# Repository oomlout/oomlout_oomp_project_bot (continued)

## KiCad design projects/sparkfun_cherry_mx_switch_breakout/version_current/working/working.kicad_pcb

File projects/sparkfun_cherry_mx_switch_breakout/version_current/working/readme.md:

# OOMP Project  
## Cherry_MX_Switch_Breakout  by sparkfun  
  
oomp key: oomp_projects_flat_sparkfun_cherry_mx_switch_breakout  
(snippet of original readme)  
  
SparkFun Cherry MX Switch Breakout  
====================  
  
<table class="table table-hover table-striped table-bordered">  
  <tr align="center">  
   <td></td>  
   <td></td>  
  </tr>  
  <tr align="center">  
    <td><i>SparkFun Cherry MX Switch Breakout </i></td>  
    <td><i>Cherry MX Switch Soldered on Breakout</i></td>  
  </tr>  
</table>  
  
[*SparkFun Cherry MX Switch Breakout (BOB-13773)*](https://www.sparkfun.com/products/13773)  
  
Cherry MX Keyswitches are top-of-the-line mechanical keyboard switches. They’re satisfyingly “clicky”, reliable up to tens-of-millions of key presses, and a standard in gaming and programming keyboards across the globe. With the SparkFun Cherry MX Switch Breakout we have made the switches more easily adaptable to breadboard or perfboard-based projects. The Cherry MX Switch Breakout is a perfect prototyping tool for projects ranging from a single-key user-input to fully-custom 101-key keyboards.  
  
Repository Contents  
-------------------  
  
* **/Hardware** - All Eagle design files (.brd, .sch)  
* **/Production** - Production panel files (.brd)  
  
Documentation  
--------------  
* **[Hookup Guide](https://learn.sparkfun.com/tutorials/cherr  
  full source readme at [readme_src.md](readme_src.md)  
  
source repo at: [https://github.com/sparkfun/Cherry_MX_Switch_Breakout](https://github.com/sparkfun/Cherry_MX_Switch_Breakout)  
## Board  

## Schematic  

[schematic pdf](working_schematic.pdf)  
## Images

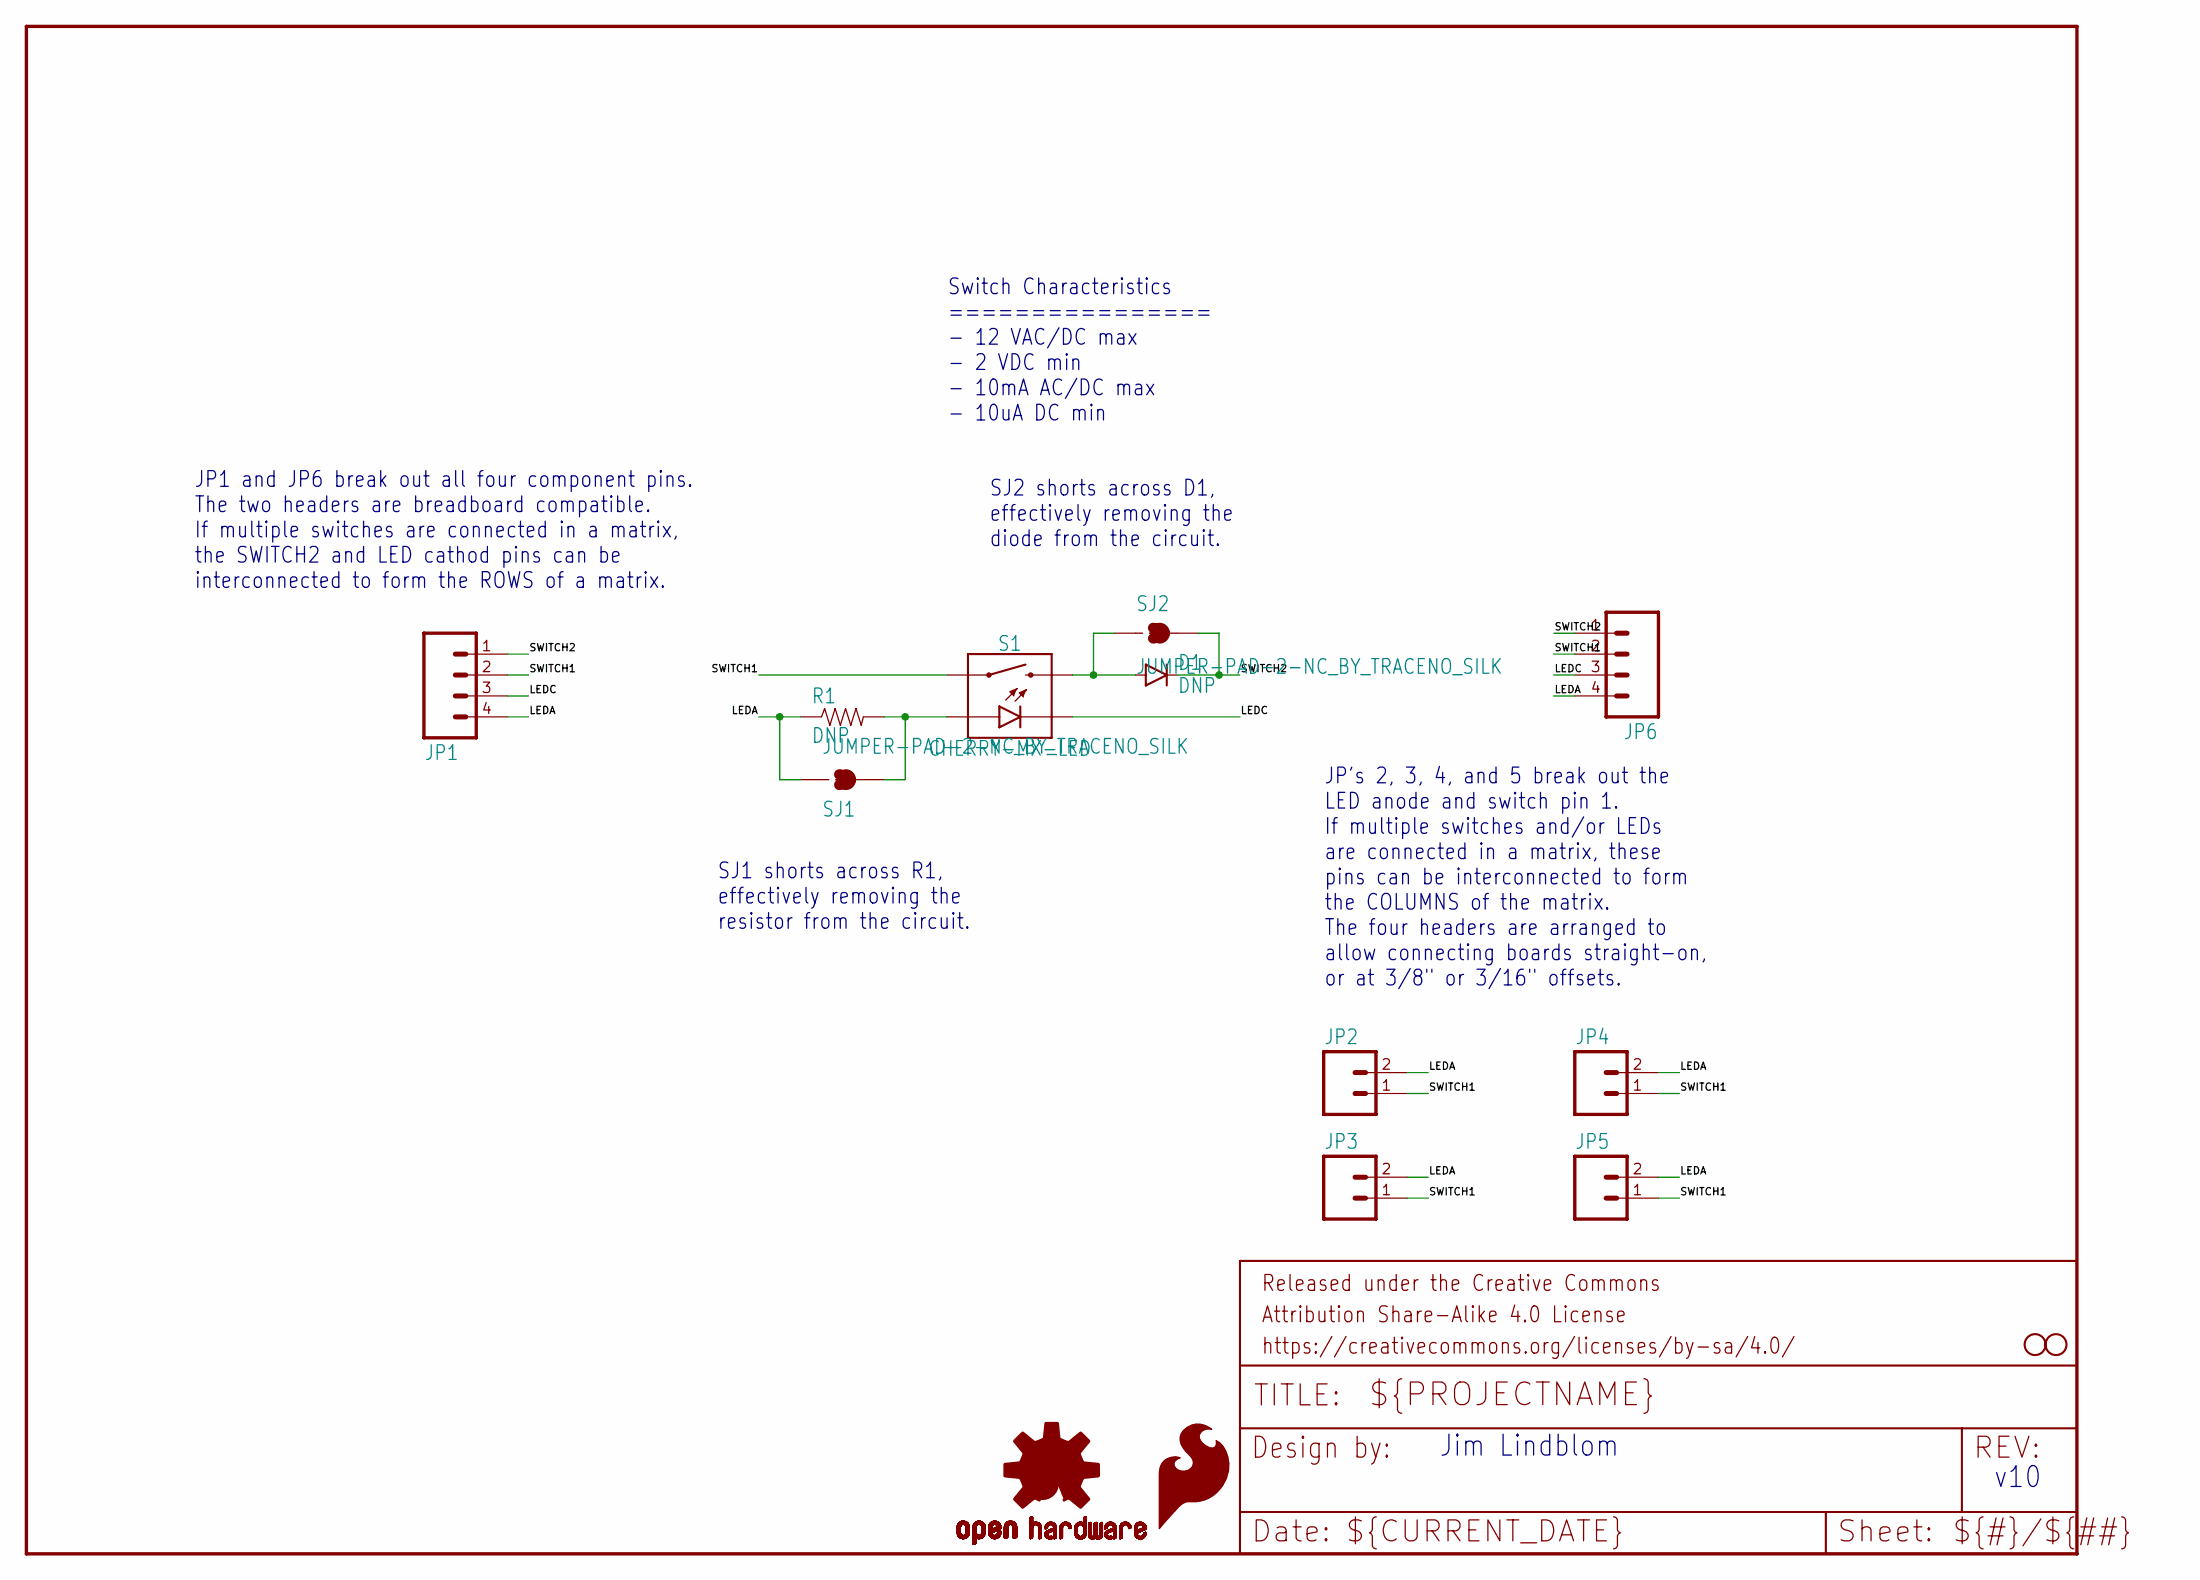
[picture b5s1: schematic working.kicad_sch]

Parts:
D1: DNP; DIODE-PTH-0.1
FRAME1: FRAME-LETTER; CREATIVE_COMMONS
JP1, JP6: M04NO_SILK_ALL_ROUND; 1X04_NO_SILK_ALL_ROUND
JP2, JP3, JP4, JP5: M021X02_NO_SILK; 1X02_NO_SILK
LOGO1: OSHW-LOGOS; OSHW-LOGO-S
LOGO2: SFE_LOGO_FLAME.1_INCH; SFE_LOGO_FLAME_.1
R1: DNP; AXIAL-0.1
S1: CHERRY-MX-LED
SJ1, SJ2: JUMPER-PAD-2-NC_BY_TRACENO_SILK; PAD-JUMPER-2-NC_BY_TRACE_NO_SILK
STANDOFF1, STANDOFF2: STAND-OFF2-56; STAND-OFF-2-56

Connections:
LEDA: JP1.4, JP2.2, JP3.2, JP4.2, JP5.2, JP6.4, R1.P$1 (1), SJ1.1
LEDC: JP1.3, JP6.3, S1.K (C)
unnamed: R1.P$2 (2), S1.A, SJ1.2
unnamed: D1.A, S1.S2, SJ2.1
SWITCH1: JP1.2, JP2.1, JP3.1, JP4.1, JP5.1, JP6.2, S1.S1
SWITCH2: D1.C, JP1.1, JP6.1, SJ2.2

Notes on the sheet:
SJ2 shorts across D1, effectively removing the diode from the circuit.
JP1 and JP6 break out all four component pins. The two headers are breadboard compatible. If multiple switches are connected in a matrix, the SWITCH2 and LED cathod pins can be interconnected to form the ROWS of a matrix.
v10
JP's 2, 3, 4, and 5 break out the LED anode and switch pin 1. If multiple switches and/or LEDs are connected in a matrix, these pins can be interconnected to form the COLUMNS of the matrix. The four headers are arranged to allow connecting boards straight-on, or at 3/8" or 3/16" offsets.
Jim Lindblom
SJ1 shorts across R1, effectively removing the resistor from the circuit.
Switch Characteristics ================ - 12 VAC/DC max - 2 VDC min - 10mA AC/DC max - 10uA DC min

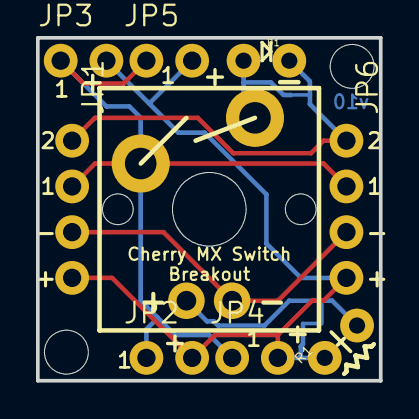
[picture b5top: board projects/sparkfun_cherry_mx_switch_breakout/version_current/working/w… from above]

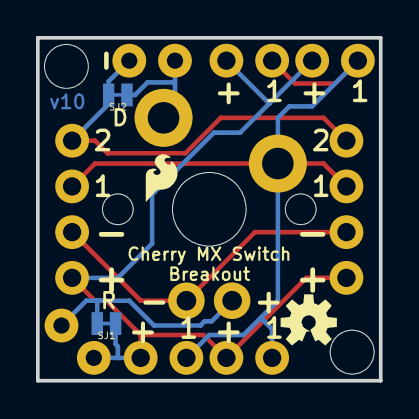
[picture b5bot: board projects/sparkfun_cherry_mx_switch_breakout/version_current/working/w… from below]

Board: 2 copper layers, 19.1 x 19.0 mm, 16 parts (4 on the bottom side), 6 nets.

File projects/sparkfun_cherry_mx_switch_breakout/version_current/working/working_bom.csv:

Row,Description,Part,References,Value,Footprint,Quantity Per PCB,Status,Datasheet
1,,FRAME-LETTER,FRAME1,FRAME-LETTER,CREATIVE_COMMONS,1, ,
2,,M021X02_NO_SILK,JP2 JP3 JP4 JP5,M021X02_NO_SILK,1X02_NO_SILK,4, ,
3,,M04NO_SILK_ALL_ROUND,JP1 JP6,M04NO_SILK_ALL_ROUND,1X04_NO_SILK_ALL_ROUND,2, ,
4,,OSHW-LOGOS,LOGO1,OSHW-LOGOS,OSHW-LOGO-S,1, ,
5,,SFE_LOGO_FLAME.1_INCH,LOGO2,SFE_LOGO_FLAME.1_INCH,SFE_LOGO_FLAME_.1,1, ,
6,,CHERRY-MX-LED,S1,CHERRY-MX-LED,CHERRY-MX-LED,1, ,
7,,JUMPER-PAD-2-NC_BY_TRACENO_SILK,SJ1 SJ2,JUMPER-PAD-2-NC_BY_TRACENO_SILK,PAD-JUMPER-2-NC_BY_TRACE_NO_SILK,2, ,
8,,STAND-OFF2-56,STANDOFF1 STANDOFF2,STAND-OFF2-56,STAND-OFF-2-56,2, ,





Project info:
Schematic:,working
Variant:,default
Revision:,
Date:,2023-08-06_12-56-00
KiCad Version:,7.0.6-7.0.6~ubuntu22.04.1
Statistics:
Component Groups:,10
Component Count:,16 (0 SMD/ 0 THT)
Fitted Components:,14 (0 SMD/ 0 THT)
Number of PCBs:,1
Total Components:,14

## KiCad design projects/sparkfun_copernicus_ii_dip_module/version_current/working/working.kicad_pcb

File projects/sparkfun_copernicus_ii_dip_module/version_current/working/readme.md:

# OOMP Project  
## Copernicus_II_DIP_Module  by sparkfun  
  
oomp key: oomp_projects_flat_sparkfun_copernicus_ii_dip_module  
(snippet of original readme)  
  
Copernicus II DIP Module  
========================  

[*Copernicus II DIP Module (GPS-11858)*](https://www.sparkfun.com/products/11858)  
  
This breakout board allows access to the SMD pins of the Copernicus II GPS module from Trimble.   
  
Repository Contents  
-------------------  
* **/Hardware** - All Eagle design files (.brd, .sch)  
* **/Libraries** - All Arduino libraries and board examples  
* **/Production** - Test bed files and production panel files  
  
Documentation  
-------------------  
* **[Hookup Guide](https://learn.sparkfun.com/tutorials/copernicus-ii-hookup-guide)** - Basic hookup guide  
  
Version History  
---------------  
* [GPS-11067 - v13](https://github.com/sparkfun/Copernicus_II_DIP_Module/tree/79d04dc032e8ecc2a1069bf3677cde6e07c77bf1)  
  
License Information  
-------------------  
The hardware is released under [Creative Commons Share-alike 3.0](http://creativecommons.org/licenses/by-sa/3.0/).   
All other code is open source so please feel free to do anything you want with it; you buy me a beer if you use this and we meet someday ([Beerware license](http://en.wikipedia.org/wiki/Beerware)).  
  
The library was written by @trbabb. The original repository can be found [here](https://github.com/trbabb/copernicus).   
  
  full source readme at [readme_src.md](readme_src.md)  
  
source repo at: [https://github.com/sparkfun/Copernicus_II_DIP_Module](https://github.com/sparkfun/Copernicus_II_DIP_Module)  
## Board  

## Schematic  

[schematic pdf](working_schematic.pdf)  
## Images

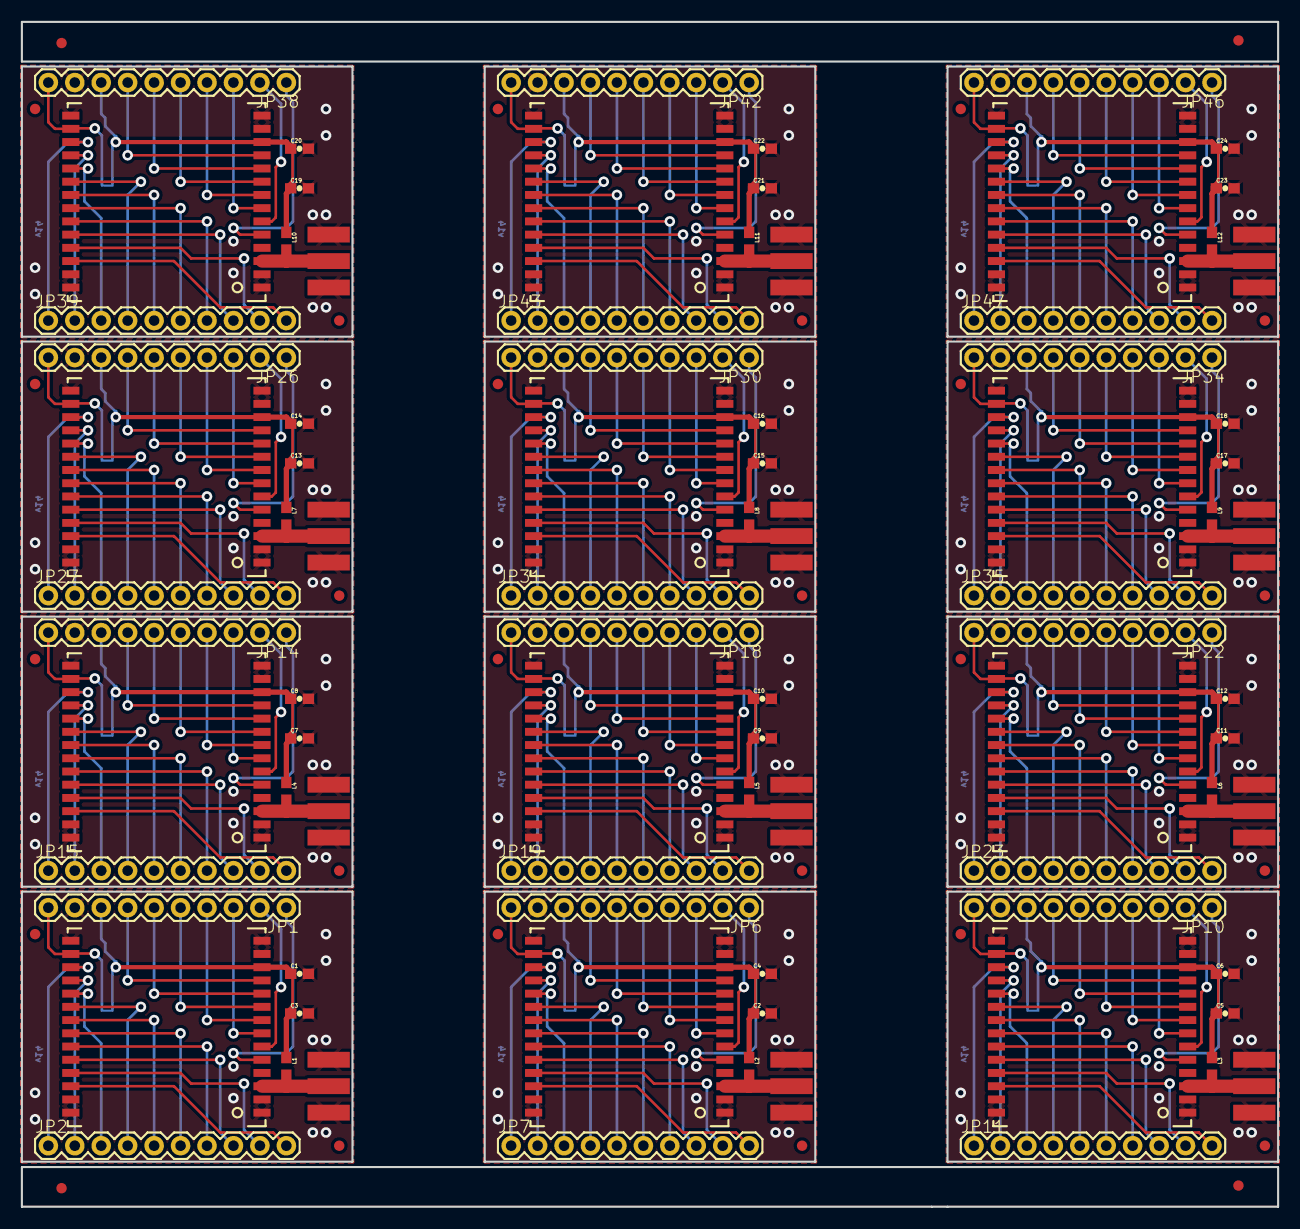
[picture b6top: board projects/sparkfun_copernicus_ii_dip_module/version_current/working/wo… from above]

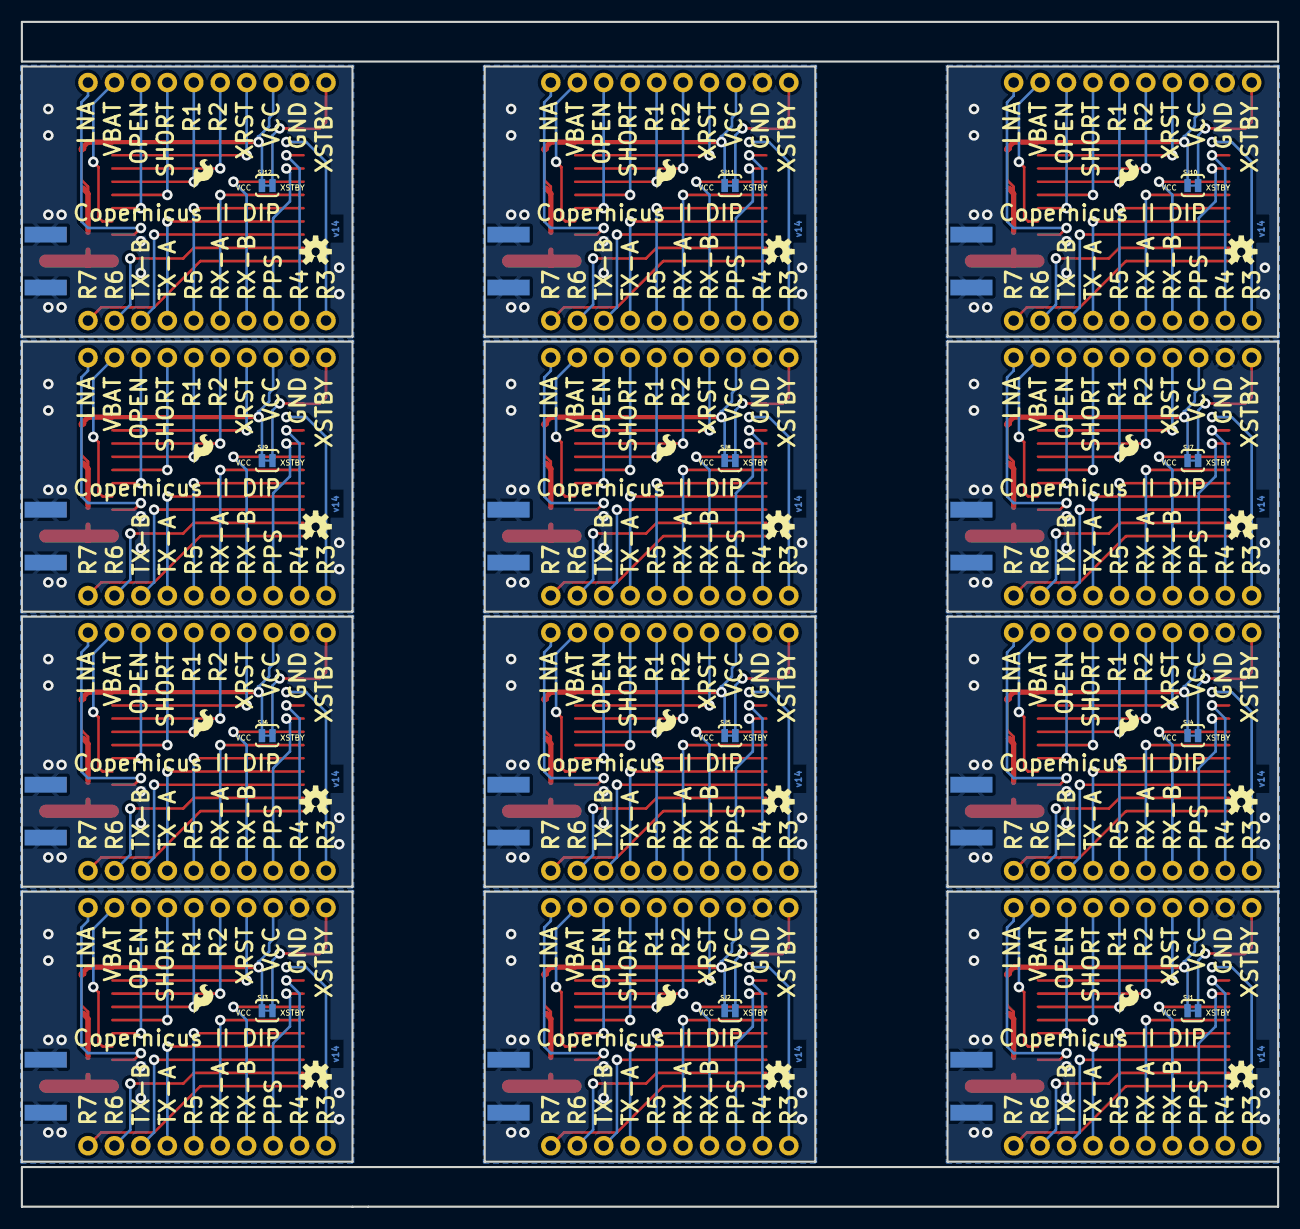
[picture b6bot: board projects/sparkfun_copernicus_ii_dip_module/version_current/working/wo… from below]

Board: 2 copper layers, 120.6 x 113.8 mm, 148 parts (36 on the bottom side), 252 nets.

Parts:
C1, C4, C6, C8, C10, C12, C14, C16, C18, C20, C22, C24: 0.1uF; 0603-CAP
C2, C3, C5, C7, C9, C11, C13, C15, C17, C19, C21, C23: 22pF; 0603-CAP
E$1, E$2, E$3, E$4: FIDUCIAL-1X2
JP1, JP2, JP6, JP7, JP10, JP11, JP14, JP15, JP18, JP19, JP22, JP23, JP26, JP27, JP30, JP31, JP34, JP35, JP38, JP39, JP42, JP43, JP46, JP47: 1X10
JP3, JP5, JP9, JP13, JP17, JP21, JP25, JP29, JP33, JP37, JP41, JP45: SMA_EDGE
JP4, JP8, JP12, JP16, JP20, JP24, JP28, JP32, JP36, JP40, JP44, JP48: LOGO-SFESK; SFE-LOGO-FLAME
L1, L2, L3, L4, L5, L6, L7, L8, L9, L10, L11, L12: 33nH; 0603
SJ1, SJ2, SJ3, SJ4, SJ5, SJ6, SJ7, SJ8, SJ9, SJ10, SJ11, SJ12: SOLDERJUMPERTRACE; SJ_2S-TRACE
U1, U2, U3, U4, U5, U6, U7, U8, U9, U10, U11, U12: COPERNICUS
U$1, U$6, U$9, U$12, U$15, U$18, U$21, U$24, U$27, U$30, U$33, U$36: OSHW-LOGOS; OSHW-LOGO-S
U$2, U$3, U$4, U$5, U$7, U$8, U$10, U$11, U$13, U$14, U$16, U$17, U$19, U$20, U$22, U$23, U$25, U$26, U$28, U$29, U$31, U$32, U$34, U$35: FIDUCIAL1X2; FIDUCIAL-1X2

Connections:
GND: C1.2, C3.2, JP1.9, JP3.GND@0, JP3.GND@1, JP3.GND@2, JP3.GND@3, U1.1, U1.2, U1.4, U1.13, U1.14, U1.15, U1.27, U1.28
GND1: C2.2, C4.2, JP5.GND@0, JP5.GND@1, JP5.GND@2, JP5.GND@3, JP6.9, U2.1, U2.2, U2.4, U2.13, U2.14, U2.15, U2.27, U2.28
GND2: C5.2, C6.2, JP9.GND@0, JP9.GND@1, JP9.GND@2, JP9.GND@3, JP10.9, U3.1, U3.2, U3.4, U3.13, U3.14, U3.15, U3.27, U3.28
GND3: C7.2, C8.2, JP13.GND@0, JP13.GND@1, JP13.GND@2, JP13.GND@3, JP14.9, U4.1, U4.2, U4.4, U4.13, U4.14, U4.15, U4.27, U4.28
GND4: C9.2, C10.2, JP17.GND@0, JP17.GND@1, JP17.GND@2, JP17.GND@3, JP18.9, U5.1, U5.2, U5.4, U5.13, U5.14, U5.15, U5.27, U5.28
GND5: C11.2, C12.2, JP21.GND@0, JP21.GND@1, JP21.GND@2, JP21.GND@3, JP22.9, U6.1, U6.2, U6.4, U6.13, U6.14, U6.15, U6.27, U6.28
GND6: C13.2, C14.2, JP25.GND@0, JP25.GND@1, JP25.GND@2, JP25.GND@3, JP26.9, U7.1, U7.2, U7.4, U7.13, U7.14, U7.15, U7.27, U7.28
GND7: C15.2, C16.2, JP29.GND@0, JP29.GND@1, JP29.GND@2, JP29.GND@3, JP30.9, U8.1, U8.2, U8.4, U8.13, U8.14, U8.15, U8.27, U8.28
GND8: C17.2, C18.2, JP33.GND@0, JP33.GND@1, JP33.GND@2, JP33.GND@3, JP34.9, U9.1, U9.2, U9.4, U9.13, U9.14, U9.15, U9.27, U9.28
GND9: C19.2, C20.2, JP37.GND@0, JP37.GND@1, JP37.GND@2, JP37.GND@3, JP38.9, U10.1, U10.2, U10.4, U10.13, U10.14, U10.15, U10.27, U10.28
GND10: C21.2, C22.2, JP41.GND@0, JP41.GND@1, JP41.GND@2, JP41.GND@3, JP42.9, U11.1, U11.2, U11.4, U11.13, U11.14, U11.15, U11.27, U11.28
GND11: C23.2, C24.2, JP45.GND@0, JP45.GND@1, JP45.GND@2, JP45.GND@3, JP46.9, U12.1, U12.2, U12.4, U12.13, U12.14, U12.15, U12.27, U12.28
LNA: JP1.1, U1.5
LNA1: JP6.1, U2.5
LNA2: JP10.1, U3.5
LNA3: JP14.1, U4.5
LNA4: JP18.1, U5.5
LNA5: JP22.1, U6.5
LNA6: JP26.1, U7.5
LNA7: JP30.1, U8.5
LNA8: JP34.1, U9.5
LNA9: JP38.1, U10.5
LNA10: JP42.1, U11.5
LNA11: JP46.1, U12.5
OPEN: JP1.3, U1.7
OPEN1: JP6.3, U2.7
OPEN2: JP10.3, U3.7
OPEN3: JP14.3, U4.7
OPEN4: JP18.3, U5.7
OPEN5: JP22.3, U6.7
OPEN6: JP26.3, U7.7
OPEN7: JP30.3, U8.7
OPEN8: JP34.3, U9.7
OPEN9: JP38.3, U10.7
OPEN10: JP42.3, U11.7
OPEN11: JP46.3, U12.7
PPS: JP2.3, U1.19
PPS1: JP7.3, U2.19
PPS2: JP11.3, U3.19
PPS3: JP15.3, U4.19
PPS4: JP19.3, U5.19
PPS5: JP23.3, U6.19
PPS6: JP27.3, U7.19
PPS7: JP31.3, U8.19
PPS8: JP35.3, U9.19
PPS9: JP39.3, U10.19
PPS10: JP43.3, U11.19
PPS11: JP47.3, U12.19
R1: JP1.5, U1.9
R2: JP1.6, U1.10
R3: JP2.1, U1.17
R4: JP2.2, U1.18
R5: JP2.6, U1.22
R6: JP2.9, U1.25
R7: JP2.10, U1.26
R8: JP6.5, U2.9
R9: JP6.6, U2.10
R10: JP7.10, U2.26
R11: JP7.9, U2.25
R12: JP7.6, U2.22
R13: JP7.2, U2.18
R14: JP7.1, U2.17
R15: JP10.5, U3.9
R16: JP10.6, U3.10
R17: JP11.10, U3.26
R18: JP11.9, U3.25
R19: JP11.6, U3.22
R20: JP11.2, U3.18
R21: JP11.1, U3.17
R22: JP14.5, U4.9
R23: JP14.6, U4.10
R24: JP15.10, U4.26
R25: JP15.9, U4.25
R26: JP15.6, U4.22
R27: JP15.2, U4.18
R28: JP15.1, U4.17
R29: JP18.5, U5.9
R30: JP18.6, U5.10
R31: JP19.10, U5.26
R32: JP19.9, U5.25
R33: JP19.6, U5.22
R34: JP19.2, U5.18
R35: JP19.1, U5.17
R36: JP22.5, U6.9
R37: JP22.6, U6.10
R38: JP23.10, U6.26
R39: JP23.9, U6.25
R40: JP23.6, U6.22
R41: JP23.2, U6.18
R42: JP23.1, U6.17
R43: JP26.5, U7.9
R44: JP26.6, U7.10
R45: JP27.10, U7.26
R46: JP27.9, U7.25
R47: JP27.6, U7.22
R48: JP27.2, U7.18
R49: JP27.1, U7.17
R50: JP30.5, U8.9
R51: JP30.6, U8.10
R52: JP31.10, U8.26
R53: JP31.9, U8.25
R54: JP31.6, U8.22
R55: JP31.2, U8.18
R56: JP31.1, U8.17
R57: JP34.5, U9.9
R58: JP34.6, U9.10
R59: JP35.10, U9.26
R60: JP35.9, U9.25
R61: JP35.6, U9.22
R62: JP35.2, U9.18
R63: JP35.1, U9.17
R64: JP38.5, U10.9
R65: JP38.6, U10.10
R66: JP39.10, U10.26
R67: JP39.9, U10.25
R68: JP39.6, U10.22
R69: JP39.2, U10.18
R70: JP39.1, U10.17
R71: JP42.5, U11.9
R72: JP42.6, U11.10
R73: JP43.10, U11.26
R74: JP43.9, U11.25
R75: JP43.6, U11.22
R76: JP43.2, U11.18
R77: JP43.1, U11.17
R78: JP46.5, U12.9
R79: JP46.6, U12.10
R80: JP47.10, U12.26
R81: JP47.9, U12.25
R82: JP47.6, U12.22
R83: JP47.2, U12.18
R84: JP47.1, U12.17
RFIN: JP3.SIG, L1.2, U1.3
RFIN1: JP5.SIG, L2.2, U2.3
RFIN2: JP9.SIG, L3.2, U3.3
RFIN3: JP13.SIG, L4.2, U4.3
RFIN4: JP17.SIG, L5.2, U5.3
RFIN5: JP21.SIG, L6.2, U6.3
RFIN6: JP25.SIG, L7.2, U7.3
RFIN7: JP29.SIG, L8.2, U8.3
RFIN8: JP33.SIG, L9.2, U9.3
RFIN9: JP37.SIG, L10.2, U10.3
RFIN10: JP41.SIG, L11.2, U11.3
RFIN11: JP45.SIG, L12.2, U12.3
RX-A: JP2.5, U1.21
RX-A1: JP7.5, U2.21
RX-A2: JP11.5, U3.21
RX-A3: JP15.5, U4.21
RX-A4: JP19.5, U5.21
RX-A5: JP23.5, U6.21
RX-A6: JP27.5, U7.21
RX-A7: JP31.5, U8.21
RX-A8: JP35.5, U9.21
RX-A9: JP39.5, U10.21
RX-A10: JP43.5, U11.21
RX-A11: JP47.5, U12.21
RX-B: JP2.4, U1.20
RX-B1: JP7.4, U2.20
RX-B2: JP11.4, U3.20
RX-B3: JP15.4, U4.20
RX-B4: JP19.4, U5.20
RX-B5: JP23.4, U6.20
RX-B6: JP27.4, U7.20
RX-B7: JP31.4, U8.20
RX-B8: JP35.4, U9.20
RX-B9: JP39.4, U10.20
RX-B10: JP43.4, U11.20
RX-B11: JP47.4, U12.20
SHORT: JP1.4, U1.8
SHORT1: JP6.4, U2.8
SHORT2: JP10.4, U3.8
SHORT3: JP14.4, U4.8
SHORT4: JP18.4, U5.8
SHORT5: JP22.4, U6.8
SHORT6: JP26.4, U7.8
SHORT7: JP30.4, U8.8
SHORT8: JP34.4, U9.8
SHORT9: JP38.4, U10.8
SHORT10: JP42.4, U11.8
SHORT11: JP46.4, U12.8
TX-A: JP2.7, U1.23
TX-A1: JP7.7, U2.23
TX-A2: JP11.7, U3.23
TX-A3: JP15.7, U4.23
TX-A4: JP19.7, U5.23
TX-A5: JP23.7, U6.23
TX-A6: JP27.7, U7.23
TX-A7: JP31.7, U8.23
TX-A8: JP35.7, U9.23
TX-A9: JP39.7, U10.23
TX-A10: JP43.7, U11.23
TX-A11: JP47.7, U12.23
TX-B: JP2.8, U1.24
TX-B1: JP7.8, U2.24
TX-B2: JP11.8, U3.24
TX-B3: JP15.8, U4.24
TX-B4: JP19.8, U5.24
TX-B5: JP23.8, U6.24
TX-B6: JP27.8, U7.24
TX-B7: JP31.8, U8.24
TX-B8: JP35.8, U9.24
TX-B9: JP39.8, U10.24
TX-B10: JP43.8, U11.24
TX-B11: JP47.8, U12.24
VBAT: JP1.2, U1.6
VBAT1: JP6.2, U2.6
VBAT2: JP10.2, U3.6
VBAT3: JP14.2, U4.6
VBAT4: JP18.2, U5.6
VBAT5: JP22.2, U6.6
VBAT6: JP26.2, U7.6
VBAT7: JP30.2, U8.6
VBAT8: JP34.2, U9.6
VBAT9: JP38.2, U10.6
VBAT10: JP42.2, U11.6
VBAT11: JP46.2, U12.6
VCC: C1.1, C3.1, JP1.8, L1.1, SJ1.1, U1.12
VCC1: C2.1, C4.1, JP6.8, L2.1, SJ2.1, U2.12
VCC2: C5.1, C6.1, JP10.8, L3.1, SJ3.1, U3.12
VCC3: C7.1, C8.1, JP14.8, L4.1, SJ4.1, U4.12
VCC4: C9.1, C10.1, JP18.8, L5.1, SJ5.1, U5.12
VCC5: C11.1, C12.1, JP22.8, L6.1, SJ6.1, U6.12
VCC6: C13.1, C14.1, JP26.8, L7.1, SJ7.1, U7.12
VCC7: C15.1, C16.1, JP30.8, L8.1, SJ8.1, U8.12
VCC8: C17.1, C18.1, JP34.8, L9.1, SJ9.1, U9.12
VCC9: C19.1, C20.1, JP38.8, L10.1, SJ10.1, U10.12
VCC10: C21.1, C22.1, JP42.8, L11.1, SJ11.1, U11.12
VCC11: C23.1, C24.1, JP46.8, L12.1, SJ12.1, U12.12
XRST: JP1.7, U1.11
XRST1: JP6.7, U2.11
XRST2: JP10.7, U3.11
XRST3: JP14.7, U4.11
XRST4: JP18.7, U5.11
XRST5: JP22.7, U6.11
XRST6: JP26.7, U7.11
XRST7: JP30.7, U8.11
XRST8: JP34.7, U9.11
XRST9: JP38.7, U10.11
XRST10: JP42.7, U11.11
XRST11: JP46.7, U12.11
XSTBY: JP1.10, SJ1.2, U1.16
XSTBY1: JP6.10, SJ2.2, U2.16
XSTBY2: JP10.10, SJ3.2, U3.16
XSTBY3: JP14.10, SJ4.2, U4.16
XSTBY4: JP18.10, SJ5.2, U5.16
XSTBY5: JP22.10, SJ6.2, U6.16
XSTBY6: JP26.10, SJ7.2, U7.16
XSTBY7: JP30.10, SJ8.2, U8.16
XSTBY8: JP34.10, SJ9.2, U9.16
XSTBY9: JP38.10, SJ10.2, U10.16
XSTBY10: JP42.10, SJ11.2, U11.16
XSTBY11: JP46.10, SJ12.2, U12.16

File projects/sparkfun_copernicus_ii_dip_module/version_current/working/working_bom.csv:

Row,Description,Part,References,Value,Footprint,Quantity Per PCB,Status,Datasheet
1,,CAP0603-CAP,C3,22pF,0603-CAP,1, ,
2,,CAP0603-CAP,C1,0.1uF,0603-CAP,1, ,
3,,FRAME-LETTER,FRAME1,FRAME-LETTER,CREATIVE_COMMONS,1, ,
4,,LOGO-SFESK,JP4,LOGO-SFESK,SFE-LOGO-FLAME,1, ,
5,,M10{dblquote},JP1 JP2,M10{dblquote},1X10,2, ,
6,,SMA_EDGE,JP3,SMA_EDGE,SMA_EDGE,1, ,
7,,INDUCTOR0603,L1,33nH,0603,1, ,
8,,COPERNICUSSMD,U1,COPERNICUSSMD,COPERNICUS,1, ,
9,,OSHW-LOGOS,U$1,OSHW-LOGOS,OSHW-LOGO-S,1, ,





Project info:
Schematic:,working
Variant:,default
Revision:,
Date:,2023-08-06_12-56-00
KiCad Version:,7.0.6-7.0.6~ubuntu22.04.1
Statistics:
Component Groups:,9
Component Count:,10 (0 SMD/ 0 THT)
Fitted Components:,10 (0 SMD/ 0 THT)
Number of PCBs:,1
Total Components:,10

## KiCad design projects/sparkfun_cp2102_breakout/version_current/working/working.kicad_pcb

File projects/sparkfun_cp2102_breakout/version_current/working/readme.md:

# CP2102_Breakout by sparkfun  
This is a harvested standardized copy of a project from github.  
The original project can be found at:  
https://github.com/sparkfun/CP2102_Breakout  
Please consult that link for additional, details, files, and license information.  
Note: It was auto harvested and if the original repo had more than one board file or anything out of the ordinary the files here are likely not representative.

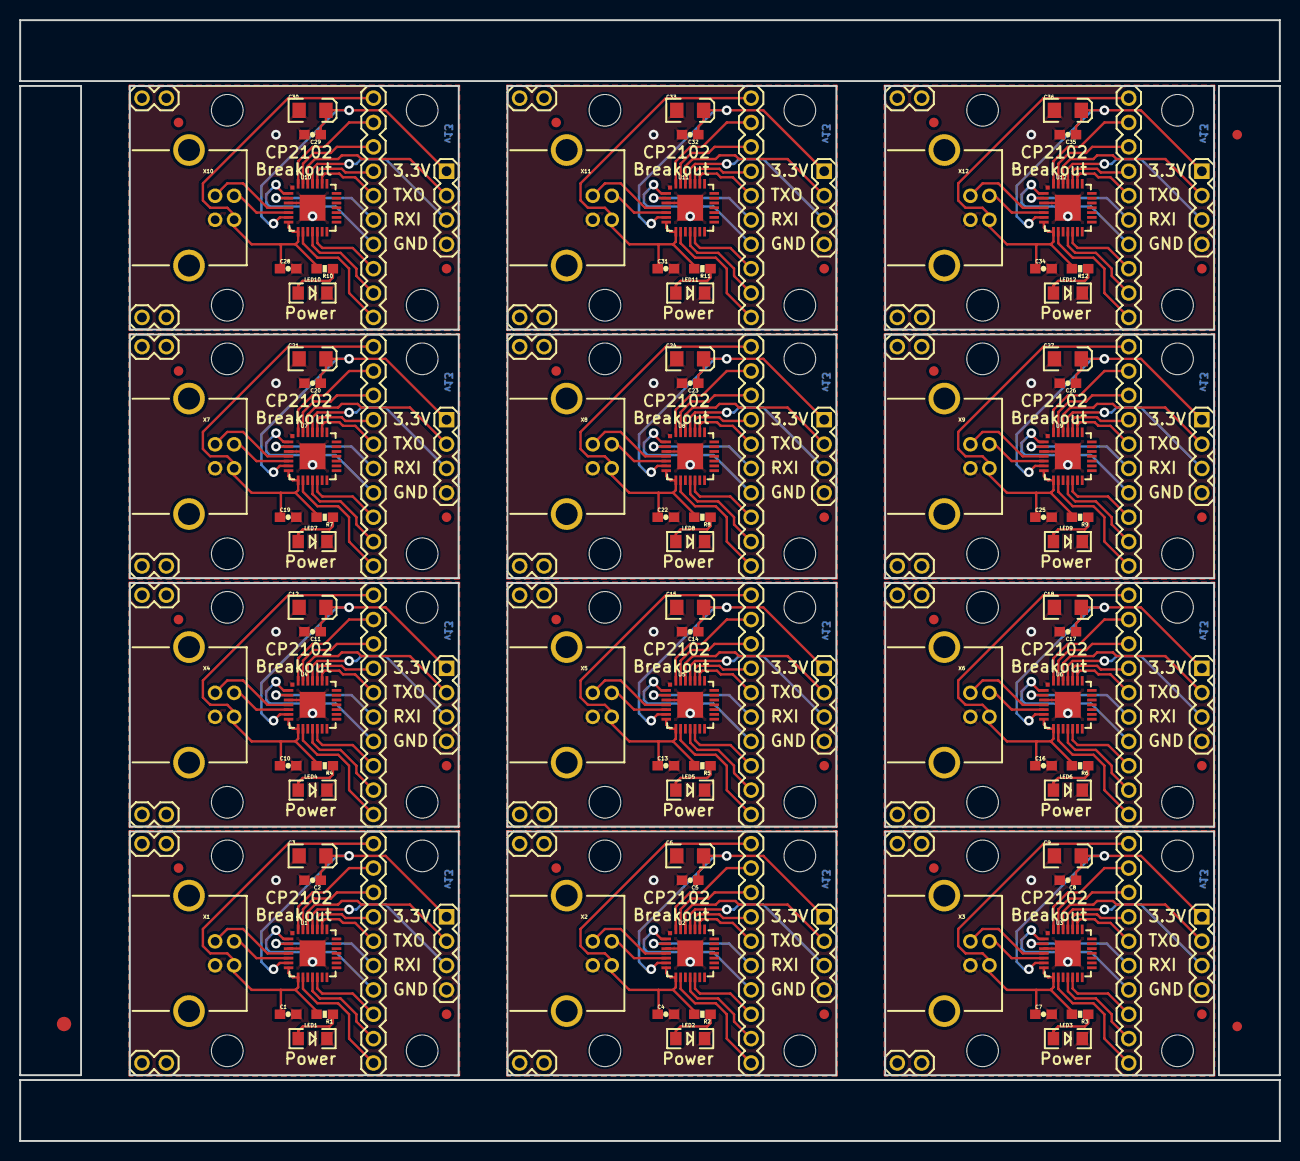
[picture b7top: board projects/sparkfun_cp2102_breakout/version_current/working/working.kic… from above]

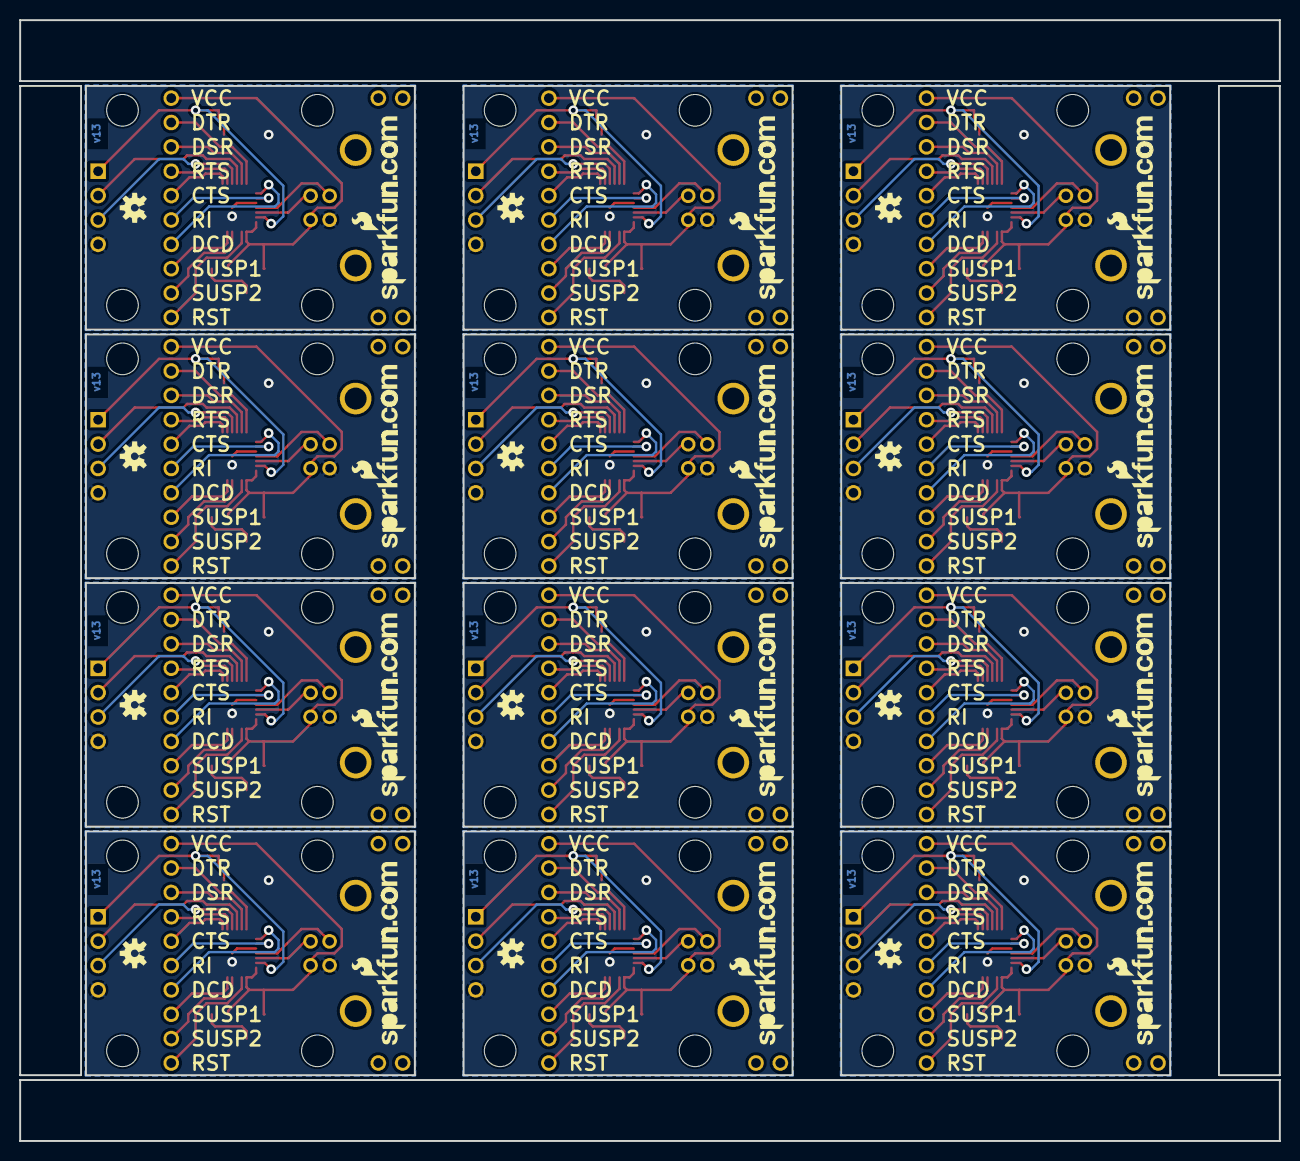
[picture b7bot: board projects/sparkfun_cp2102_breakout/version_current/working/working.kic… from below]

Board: 2 copper layers, 131.3 x 116.8 mm, 231 parts (24 on the bottom side), 204 nets.

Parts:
C1, C4, C7, C10, C13, C16, C19, C22, C25, C28, C31, C34: 1uF; 0603-CAP
C2, C5, C8, C11, C14, C17, C20, C23, C26, C29, C32, C35: 0.1uF; 0603-CAP
C3, C6, C9, C12, C15, C18, C21, C24, C27, C30, C33, C36: 10uF; EIA3216
E$1: FIDUCIAL-1.5X3
E$6, E$7: FIDUCIAL-1X2
FID1, FID2, FID3, FID4, FID5, FID6, FID7, FID8, FID9, FID10, FID11, FID12, FID13, FID14, FID15, FID16, FID17, FID18, FID19, FID20, FID21, FID22, FID23, FID24: FIDUCIAL1X2; FIDUCIAL-1X2
JP1, JP2, JP5, JP6, JP9, JP10, JP13, JP14, JP17, JP18, JP21, JP22, JP25, JP26, JP29, JP30, JP33, JP34, JP37, JP38, JP41, JP42, JP45, JP46: 1X02
JP3, JP7, JP11, JP15, JP19, JP23, JP27, JP31, JP35, JP39, JP43, JP47: 1X04
JP4, JP8, JP12, JP16, JP20, JP24, JP28, JP32, JP36, JP40, JP44, JP48: M100.1; 1X10
LED1, LED2, LED3, LED4, LED5, LED6, LED7, LED8, LED9, LED10, LED11, LED12: Red; LED-1206
LOGO1, LOGO2, LOGO3, LOGO4, LOGO5, LOGO6, LOGO7, LOGO8, LOGO9, LOGO10, LOGO11, LOGO12: OSHW-LOGOS; OSHW-LOGO-S
R1, R2, R3, R4, R5, R6, R7, R8, R9, R10, R11, R12: 330; 0603-RES
U1, U2, U3, U4, U5, U6, U7, U8, U9, U10, U11, U12: CP2102; MLP28
U$1, U$2, U$11, U$16, U$21, U$26, U$31, U$36, U$41, U$46, U$51, U$56: LOGO-SFENEW; SFE-NEW-WEBLOGO
U$3, U$4, U$5, U$6, U$7, U$8, U$9, U$10, U$12, U$13, U$14, U$15, U$17, U$18, U$19, U$20, U$22, U$23, U$24, U$25, U$27, U$28, U$29, U$30, U$32, U$33, U$34, U$35, U$37, U$38, U$39, U$40, U$42, U$43, U$44, U$45, U$47, U$48, U$49, U$50, U$52, U$53, U$54, U$55, U$57, U$58, U$59, U$60: STAND-OFF
X1, X2, X3, X4, X5, X6, X7, X8, X9, X10, X11, X12: USBPTH; USB-B-PTH

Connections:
3.3V: C2.1, C3.A, JP3.1, U1.6
3.3V1: C5.1, C6.A, JP7.1, U2.6
3.3V2: C8.1, C9.A, JP11.1, U3.6
3.3V3: C11.1, C12.A, JP15.1, U4.6
3.3V4: C14.1, C15.A, JP19.1, U5.6
3.3V5: C17.1, C18.A, JP23.1, U6.6
3.3V6: C20.1, C21.A, JP27.1, U7.6
3.3V7: C23.1, C24.A, JP31.1, U8.6
3.3V8: C26.1, C27.A, JP35.1, U9.6
3.3V9: C29.1, C30.A, JP39.1, U10.6
3.3V10: C32.1, C33.A, JP43.1, U11.6
3.3V11: C35.1, C36.A, JP47.1, U12.6
CTS: JP4.5, U1.23
CTS1: JP8.5, U2.23
CTS2: JP12.5, U3.23
CTS3: JP16.5, U4.23
CTS4: JP20.5, U5.23
CTS5: JP24.5, U6.23
CTS6: JP28.5, U7.23
CTS7: JP32.5, U8.23
CTS8: JP36.5, U9.23
CTS9: JP40.5, U10.23
CTS10: JP44.5, U11.23
CTS11: JP48.5, U12.23
DCD: JP4.7, U1.1
DCD1: JP8.7, U2.1
DCD2: JP12.7, U3.1
DCD3: JP16.7, U4.1
DCD4: JP20.7, U5.1
DCD5: JP24.7, U6.1
DCD6: JP28.7, U7.1
DCD7: JP32.7, U8.1
DCD8: JP36.7, U9.1
DCD9: JP40.7, U10.1
DCD10: JP44.7, U11.1
DCD11: JP48.7, U12.1
DSR: JP4.3, U1.27
DSR1: JP8.3, U2.27
DSR2: JP12.3, U3.27
DSR3: JP16.3, U4.27
DSR4: JP20.3, U5.27
DSR5: JP24.3, U6.27
DSR6: JP28.3, U7.27
DSR7: JP32.3, U8.27
DSR8: JP36.3, U9.27
DSR9: JP40.3, U10.27
DSR10: JP44.3, U11.27
DSR11: JP48.3, U12.27
DTR: JP4.2, U1.28
DTR1: JP8.2, U2.28
DTR2: JP12.2, U3.28
DTR3: JP16.2, U4.28
DTR4: JP20.2, U5.28
DTR5: JP24.2, U6.28
DTR6: JP28.2, U7.28
DTR7: JP32.2, U8.28
DTR8: JP36.2, U9.28
DTR9: JP40.2, U10.28
DTR10: JP44.2, U11.28
DTR11: JP48.2, U12.28
GND: C1.2, C2.2, C3.C, JP3.4, LED1.C, U1.3, U1.EXP, U1.M, X1.GND
GND1: C4.2, C5.2, C6.C, JP7.4, LED2.C, U2.3, U2.EXP, U2.M, X2.GND
GND2: C7.2, C8.2, C9.C, JP11.4, LED3.C, U3.3, U3.EXP, U3.M, X3.GND
GND3: C10.2, C11.2, C12.C, JP15.4, LED4.C, U4.3, U4.EXP, U4.M, X4.GND
GND4: C13.2, C14.2, C15.C, JP19.4, LED5.C, U5.3, U5.EXP, U5.M, X5.GND
GND5: C16.2, C17.2, C18.C, JP23.4, LED6.C, U6.3, U6.EXP, U6.M, X6.GND
GND6: C19.2, C20.2, C21.C, JP27.4, LED7.C, U7.3, U7.EXP, U7.M, X7.GND
GND7: C22.2, C23.2, C24.C, JP31.4, LED8.C, U8.3, U8.EXP, U8.M, X8.GND
GND8: C25.2, C26.2, C27.C, JP35.4, LED9.C, U9.3, U9.EXP, U9.M, X9.GND
GND9: C28.2, C29.2, C30.C, JP39.4, LED10.C, U10.3, U10.EXP, U10.M, X10.GND
GND10: C31.2, C32.2, C33.C, JP43.4, LED11.C, U11.3, U11.EXP, U11.M, X11.GND
GND11: C34.2, C35.2, C36.C, JP47.4, LED12.C, U12.3, U12.EXP, U12.M, X12.GND
unnamed: U1.5, X1.D-
unnamed: U1.4, X1.D+
unnamed: LED1.A, R1.1
unnamed: U2.5, X2.D-
unnamed: U2.4, X2.D+
unnamed: LED2.A, R2.1
unnamed: U3.5, X3.D-
unnamed: U3.4, X3.D+
unnamed: LED3.A, R3.1
unnamed: U4.5, X4.D-
unnamed: U4.4, X4.D+
unnamed: LED4.A, R4.1
unnamed: U5.5, X5.D-
unnamed: U5.4, X5.D+
unnamed: LED5.A, R5.1
unnamed: U6.5, X6.D-
unnamed: U6.4, X6.D+
unnamed: LED6.A, R6.1
unnamed: U7.5, X7.D-
unnamed: U7.4, X7.D+
unnamed: LED7.A, R7.1
unnamed: U8.5, X8.D-
unnamed: U8.4, X8.D+
unnamed: LED8.A, R8.1
unnamed: U9.5, X9.D-
unnamed: U9.4, X9.D+
unnamed: LED9.A, R9.1
unnamed: U10.5, X10.D-
unnamed: U10.4, X10.D+
unnamed: LED10.A, R10.1
unnamed: U11.5, X11.D-
unnamed: U11.4, X11.D+
unnamed: LED11.A, R11.1
unnamed: U12.5, X12.D-
unnamed: U12.4, X12.D+
unnamed: LED12.A, R12.1
RI: JP4.6, U1.2
RI1: JP8.6, U2.2
RI2: JP12.6, U3.2
RI3: JP16.6, U4.2
RI4: JP20.6, U5.2
RI5: JP24.6, U6.2
RI6: JP28.6, U7.2
RI7: JP32.6, U8.2
RI8: JP36.6, U9.2
RI9: JP40.6, U10.2
RI10: JP44.6, U11.2
RI11: JP48.6, U12.2
RST: JP4.10, U1.9
RST1: JP8.10, U2.9
RST2: JP12.10, U3.9
RST3: JP16.10, U4.9
RST4: JP20.10, U5.9
RST5: JP24.10, U6.9
RST6: JP28.10, U7.9
RST7: JP32.10, U8.9
RST8: JP36.10, U9.9
RST9: JP40.10, U10.9
RST10: JP44.10, U11.9
RST11: JP48.10, U12.9
RTS: JP4.4, U1.24
RTS1: JP8.4, U2.24
RTS2: JP12.4, U3.24
RTS3: JP16.4, U4.24
RTS4: JP20.4, U5.24
RTS5: JP24.4, U6.24
RTS6: JP28.4, U7.24
RTS7: JP32.4, U8.24
RTS8: JP36.4, U9.24
RTS9: JP40.4, U10.24
RTS10: JP44.4, U11.24
RTS11: JP48.4, U12.24
RX: JP3.3, U1.25
RX1: JP7.3, U2.25
RX2: JP11.3, U3.25
RX3: JP15.3, U4.25
RX4: JP19.3, U5.25
RX5: JP23.3, U6.25
RX6: JP27.3, U7.25
RX7: JP31.3, U8.25
RX8: JP35.3, U9.25
RX9: JP39.3, U10.25
RX10: JP43.3, U11.25
RX11: JP47.3, U12.25
SUSP1: JP4.8, U1.12
SUSP2: JP4.9, U1.11
SUSP3: JP8.8, U2.12
SUSP4: JP8.9, U2.11
SUSP5: JP12.8, U3.12
SUSP6: JP12.9, U3.11
SUSP7: JP16.8, U4.12
SUSP8: JP16.9, U4.11
SUSP9: JP20.8, U5.12
SUSP10: JP20.9, U5.11
SUSP11: JP24.8, U6.12
SUSP12: JP24.9, U6.11
SUSP13: JP28.8, U7.12
SUSP14: JP28.9, U7.11
SUSP15: JP32.8, U8.12
SUSP16: JP32.9, U8.11
SUSP17: JP36.8, U9.12
SUSP18: JP36.9, U9.11
SUSP19: JP40.8, U10.12
SUSP20: JP40.9, U10.11
SUSP21: JP44.8, U11.12
SUSP22: JP44.9, U11.11
SUSP23: JP48.8, U12.12
SUSP24: JP48.9, U12.11
TX: JP3.2, U1.26
TX1: JP7.2, U2.26
TX2: JP11.2, U3.26
TX3: JP15.2, U4.26
TX4: JP19.2, U5.26
TX5: JP23.2, U6.26
TX6: JP27.2, U7.26
TX7: JP31.2, U8.26
TX8: JP35.2, U9.26
TX9: JP39.2, U10.26
TX10: JP43.2, U11.26
TX11: JP47.2, U12.26
VCC: C1.1, JP4.1, R1.2, U1.7, U1.8, X1.VBUS
VCC1: C4.1, JP8.1, R2.2, U2.7, U2.8, X2.VBUS
VCC2: C7.1, JP12.1, R3.2, U3.7, U3.8, X3.VBUS
VCC3: C10.1, JP16.1, R4.2, U4.7, U4.8, X4.VBUS
VCC4: C13.1, JP20.1, R5.2, U5.7, U5.8, X5.VBUS
VCC5: C16.1, JP24.1, R6.2, U6.7, U6.8, X6.VBUS
VCC6: C19.1, JP28.1, R7.2, U7.7, U7.8, X7.VBUS
VCC7: C22.1, JP32.1, R8.2, U8.7, U8.8, X8.VBUS
VCC8: C25.1, JP36.1, R9.2, U9.7, U9.8, X9.VBUS
VCC9: C28.1, JP40.1, R10.2, U10.7, U10.8, X10.VBUS
VCC10: C31.1, JP44.1, R11.2, U11.7, U11.8, X11.VBUS
VCC11: C34.1, JP48.1, R12.2, U12.7, U12.8, X12.VBUS
